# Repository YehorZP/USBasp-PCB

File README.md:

# USBasp-PCB
Double-sided PCB layout for USBasp

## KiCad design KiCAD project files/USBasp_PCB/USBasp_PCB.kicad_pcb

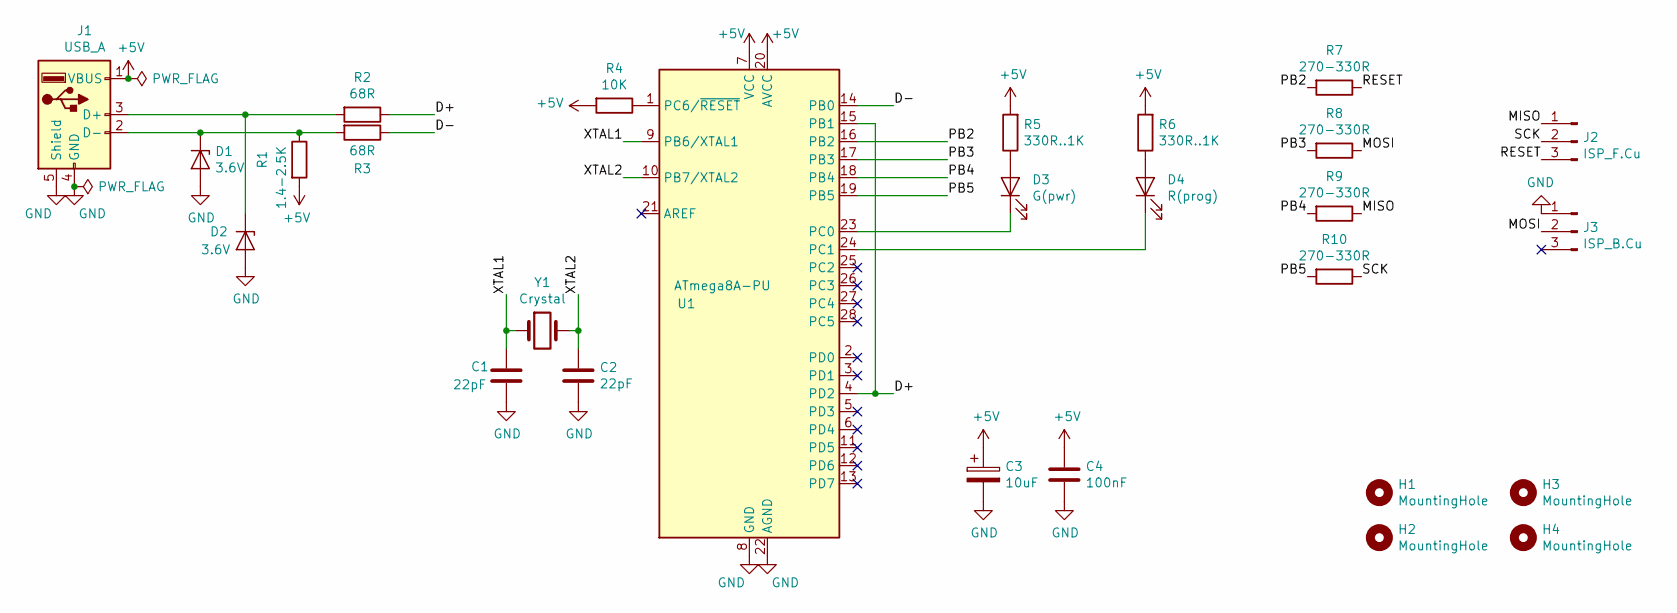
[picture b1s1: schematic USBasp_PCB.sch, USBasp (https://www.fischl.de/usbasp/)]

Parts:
C1, C2: 22pF; C_Disc_D5.1mm_W3.2mm_P5.00mm
C3: 10uF; CP_Radial_D5.0mm_P2.50mm
C4: 100nF; C_Disc_D5.1mm_W3.2mm_P5.00mm
D1, D2: 3.6V; D_DO-35_SOD27_P10.16mm_Horizontal
D3: G(pwr); LED_D3.0mm
D4: R(prog); LED_D3.0mm
H1, H2, H3, H4: MountingHole; MountingHole_2.2mm_M2
J1: USB_A; USB-A-H_PADS_NUMBERED
J2: ISP_F.Cu; PinHeader_1x03_P2.54mm_SMD_Horizontal
J3: ISP_B.Cu; PinHeader_1x03_P2.54mm_SMD_Horizontal
R1: 1.4-2.5K; R_Axial_DIN0207_L6.3mm_D2.5mm_P10.16mm_Horizontal
R2, R3: 68R; R_Axial_DIN0207_L6.3mm_D2.5mm_P10.16mm_Horizontal
R4: 10K; R_Axial_DIN0207_L6.3mm_D2.5mm_P10.16mm_Horizontal
R5, R6: 330R..1K; R_Axial_DIN0207_L6.3mm_D2.5mm_P10.16mm_Horizontal
R7, R8, R9, R10: 270-330R; R_Axial_DIN0207_L6.3mm_D2.5mm_P10.16mm_Horizontal
U1: ATmega8A-PU; DIP-28_W7.62mm_Socket_LongPads
Y1: Crystal; Crystal_HC18-U_Vertical

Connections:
+5V: C3.1, C4.1, J1.1 (VBUS), R1.2, R4.2, R5.2, R6.2, U1.7 (VCC), U1.20 (AVCC)
/D+: R2.1, U1.4 (PD2), U1.15 (PB1)
/D-: R3.1, U1.14 (PB0)
/MISO: J2.1, R9.1
/MOSI: J3.2, R8.1
/PB2: R7.2, U1.16 (PB2)
/PB3: R8.2, U1.17 (PB3)
/PB4: R9.2, U1.18 (PB4)
/PB5: R10.2, U1.19 (PB5)
/RESET: J2.3, R7.1
/SCK: J2.2, R10.1
/XTAL1: C1.1, U1.9 (PB6/XTAL1), Y1.1
/XTAL2: C2.1, U1.10 (PB7/XTAL2), Y1.2
GND: C1.2, C2.2, C3.2, C4.2, D1.2 (A), D2.2 (A), J1.4 (GND), J1.5 (Shield), J3.1, U1.8 (GND), U1.22 (AGND)
unnamed: D1.1 (K), J1.2 (D-), R1.1, R3.2
unnamed: D2.1 (K), J1.3 (D+), R2.2
unnamed: D3.1 (K), U1.23 (PC0)
unnamed: D3.2 (A), R5.1
unnamed: D4.1 (K), U1.24 (PC1)
unnamed: D4.2 (A), R6.1
unnamed: R4.1, U1.1 (PC6/~RESET)

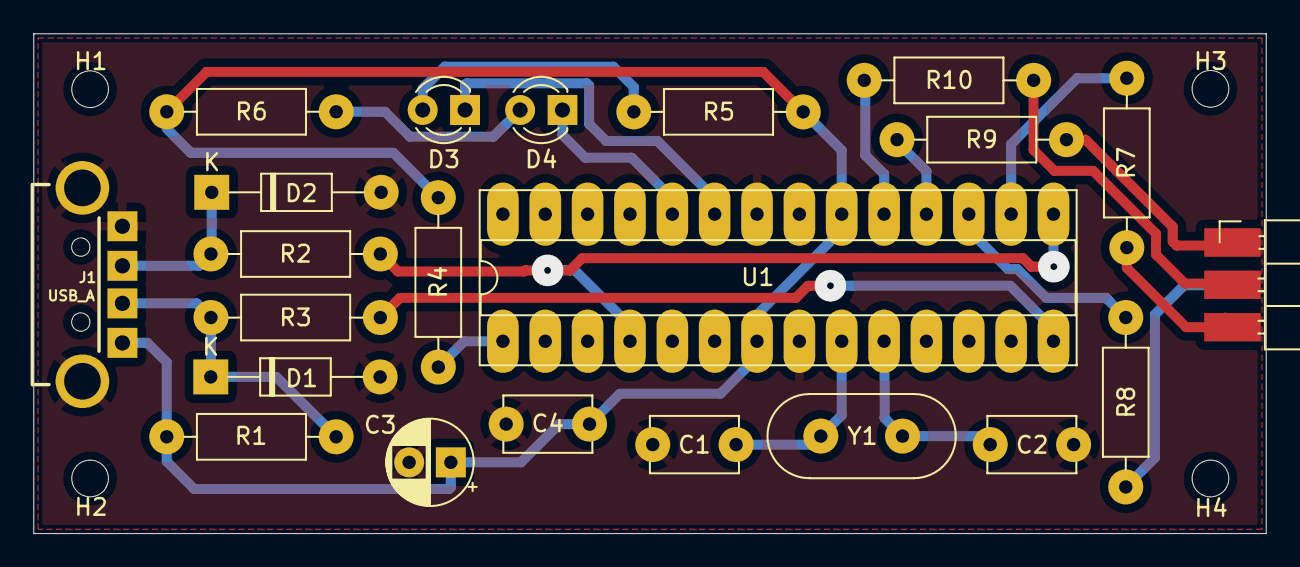
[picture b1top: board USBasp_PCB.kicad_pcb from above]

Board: 2 copper layers, 73.9 x 30.0 mm, 27 parts (1 on the bottom side), 21 nets.

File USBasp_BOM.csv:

,,
C1,22pF,Ceramic capacitor (D5.1mm_W3.2mm_P5.00mm)
C2,22pF,Ceramic capacitor (D5.1mm_W3.2mm_P5.00mm)
C3,10uF,Capacitor electrolytic (D5.0mm_P2.50mm)
C4,100nF,Ceramic capacitor (D5.1mm_W3.2mm_P5.00mm)
D1,3.6V,"Zener diode, 0.5 W (DO-35)"
D2,3.6V,"Zener diode, 0.5 W (DO-35)"
D3,G(pwr),LED_D3.0mm (green)
D4,R(prog),LED_D3.0mm (red)
J1,USB_A,Connectors:USB-A-H
J2,ISP_F.Cu,PinHeader_1x03_P2.54mm
J3,ISP_B.Cu,PinHeader_1x03_P2.54mm
R1,1.4-2.5K,Resistor Axial_DIN0207_L6.3mm_D2.5mm
R10,270-330R,Resistor Axial_DIN0207_L6.3mm_D2.5mm
R2,68R,Resistor Axial_DIN0207_L6.3mm_D2.5mm
R3,68R,Resistor Axial_DIN0207_L6.3mm_D2.5mm
R4,10K,Resistor Axial_DIN0207_L6.3mm_D2.5mm
R5,330R..1K,Resistor Axial_DIN0207_L6.3mm_D2.5mm
R6,330R..1K,Resistor Axial_DIN0207_L6.3mm_D2.5mm
R7,270-330R,Resistor Axial_DIN0207_L6.3mm_D2.5mm
R8,270-330R,Resistor Axial_DIN0207_L6.3mm_D2.5mm
R9,270-330R,Resistor Axial_DIN0207_L6.3mm_D2.5mm
U1,ATmega8A-PU,Package_DIP:DIP-28_W7.62mm_Socket_LongPads
Y1,Crystal,"HC18-U_Vertical, 12000 Hz"

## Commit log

2019-08-23 Create subfolder
